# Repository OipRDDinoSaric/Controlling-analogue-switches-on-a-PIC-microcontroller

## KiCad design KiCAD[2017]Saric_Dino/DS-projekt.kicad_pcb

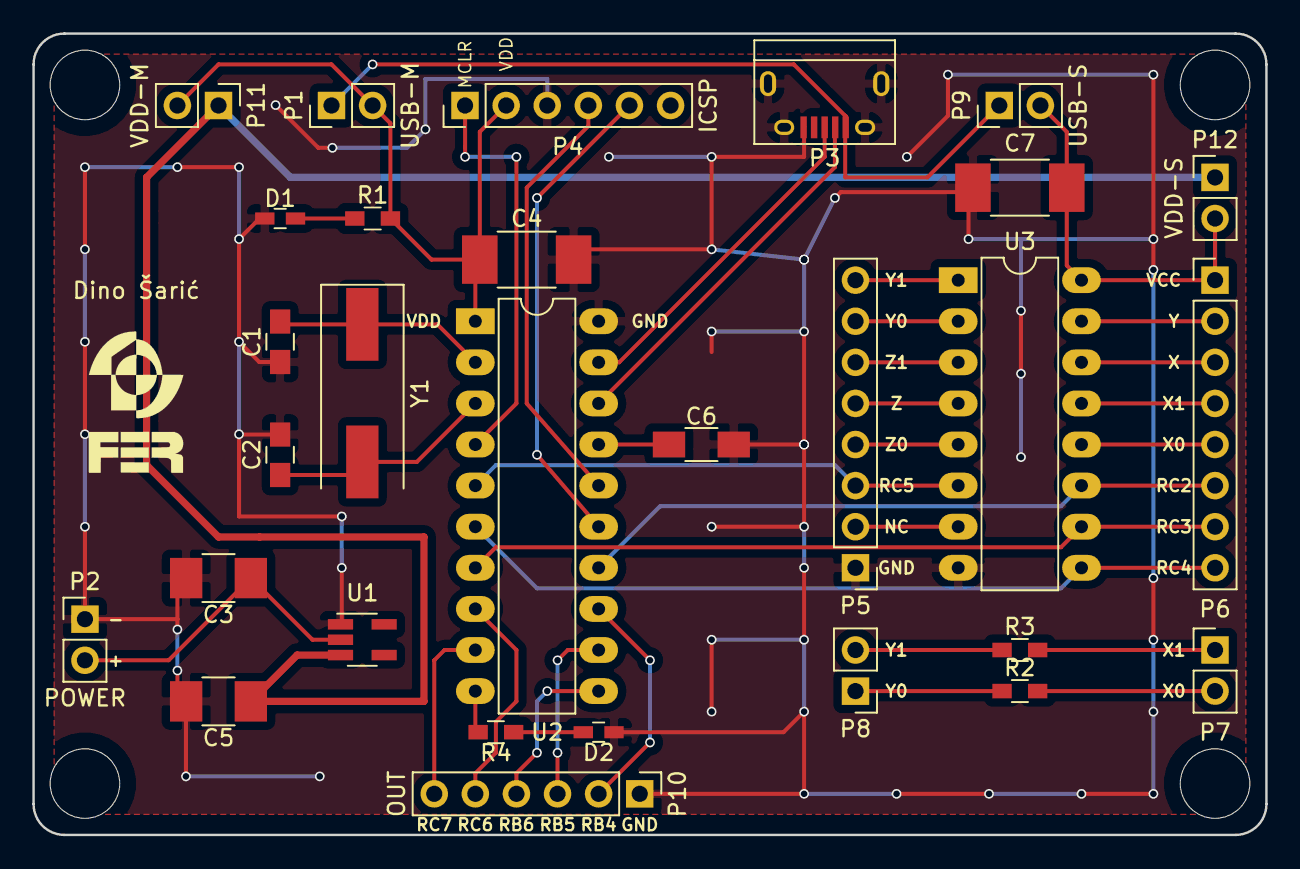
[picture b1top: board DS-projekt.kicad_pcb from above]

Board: 2 copper layers, 76.2 x 49.5 mm, 30 parts (0 on the bottom side), 40 nets.

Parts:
C1, C2: 22 p; C_0805_HandSoldering
C3: 1u; C_1210_HandSoldering
C4: 100 n; C_1812_HandSoldering
C5: 2u2; C_1210_HandSoldering
C6: 470 n; C_1206_HandSoldering
C7: 10 n; C_1812_HandSoldering
D1, D2: LED_Small; C_0603_HandSoldering
P1: USB-M; Pin_Header_Straight_1x02_Pitch2.54mm
P2: POWER; Pin_Header_Straight_1x02_Pitch2.54mm
P3: USB_OTG; USB_Micro-B
P4: ICSP; Pin_Header_Straight_1x06_Pitch2.54mm
P5, P6: CONN_01X08; Pin_Header_Straight_1x08_Pitch2.54mm
P7, P8: CONN_01X02; Pin_Header_Straight_1x02_Pitch2.54mm
P9: USB-S; Pin_Header_Straight_1x02_Pitch2.54mm
P10: OUT; Pin_Header_Straight_1x06_Pitch2.54mm
P11: VDD-M; Pin_Header_Straight_1x02_Pitch2.54mm
P12: VDD-S; Pin_Header_Straight_1x02_Pitch2.54mm
R1, R4: 150; R_0603_HandSoldering
R2: 10k; R_0603_HandSoldering
R3: 100; R_0603_HandSoldering
U1: TPS709B50DBVT; SOT-23-5_HandSoldering
U2: PIC16F1459; DIP-20_W7.62mm_LongPads
U3: MAX4619; DIP-16_W7.62mm_LongPads
VAL: FERlogov3NEGBMP_025in
Y1: Crystal; Crystal_SMD_HC49-SD

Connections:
+5V: C5.1, P11.1, P12.1, U1.3
/CLKIN: C1.2, U2.2, Y1.1
/CLKOUT: C2.1, U2.3, Y1.2
/D+: P3.3, U2.19
/D-: P3.2, U2.18
/ICSPCLK: P4.5, U2.15
/ICSPDAT: P4.4, U2.16
/MCLR: P4.1, U2.4
/RB4: P10.2, U2.13
/RB5: P10.3, U2.12
/RB6: P10.4, U2.11
/RB7: R4.1, U2.10
/RC2: P6.6, U2.14, U3.11
/RC3: P6.7, U2.7, U3.10
/RC4: P6.8, U2.6, U3.9
/RC5: P5.3, U2.5, U3.6
/RC6: P10.5, U2.8
/RC7: P10.6, U2.9
/VBUS_USB: P1.1, P3.1, P9.1
/VDD: C4.2, P1.2, P4.2, P11.2, R1.2, U2.1
/X: P6.3, U3.14
/X0: P6.5, U3.12
/X1: P6.4, U3.13
/Y: P6.2, U3.15
/Y0: P5.7, U3.2
/Y1: P5.8, U3.1
/Z: P5.5, U3.4
/Z0: P5.4, U3.5
/Z1: P5.6, U3.3
GND: C1.1, C2.2, C3.2, C4.1, C5.2, C6.2, C7.1, D1.1, D2.1, P2.1, P3.5, P3.6, P4.3, P5.1, P10.1, U1.1, U2.20, U3.8
unnamed: C3.1, P2.2, U1.2
unnamed: C6.1, U2.17
unnamed: C7.2, P6.1, P9.2, P12.2, U3.16
unnamed: D1.2, R1.1
unnamed: D2.2, R4.2
unnamed: P5.2, U3.7
unnamed: P7.1, R3.2
unnamed: P7.2, R2.2
unnamed: P8.1, R2.1
unnamed: P8.2, R3.1

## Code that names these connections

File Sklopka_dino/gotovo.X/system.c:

/*******************************************************************************
Copyright 2016 Microchip Technology Inc. (www.microchip.com)

Licensed under the Apache License, Version 2.0 (the "License");
you may not use this file except in compliance with the License.
You may obtain a copy of the License at

    http://www.apache.org/licenses/LICENSE-2.0

Unless required by applicable law or agreed to in writing, software
distributed under the License is distributed on an "AS IS" BASIS,
WITHOUT WARRANTIES OR CONDITIONS OF ANY KIND, either express or implied.
See the License for the specific language governing permissions and
limitations under the License.

To request to license the code under the MLA license (www.microchip.com/mla_license), 
please contact mla_licensing@microchip.com
*******************************************************************************/

#include "system.h"
#include "usb.h"

/** CONFIGURATION Bits **********************************************/
// PIC16F1459 configuration bit settings:
#if defined (USE_INTERNAL_OSC)	    // Define this in system.h if using the HFINTOSC for USB operation
    // CONFIG1
    #pragma config FOSC = INTOSC    // Oscillator Selection Bits (INTOSC oscillator: I/O function on CLKIN pin)
    #pragma config WDTE = OFF       // Watchdog Timer Enable (WDT disabled)
    #pragma config PWRTE = OFF      // Power-up Timer Enable (PWRT disabled)
    #pragma config MCLRE = ON       // MCLR Pin Function Select (MCLR/VPP pin function is MCLR)
    #pragma config CP = OFF         // Flash Program Memory Code Protection (Program memory code protection is disabled)
    #pragma config BOREN = OFF      // Brown-out Reset Enable (Brown-out Reset disabled)
    #pragma config CLKOUTEN = ON    // Clock Out Enable (CLKOUT function is enabled on the CLKOUT pin)
    #pragma config IESO = OFF       // Internal/External Switchover Mode (Internal/External Switchover Mode is disabled)
    #pragma config FCMEN = OFF      // Fail-Safe Clock Monitor Enable (Fail-Safe Clock Monitor is disabled)

    // CONFIG2
    #pragma config WRT = OFF        // Flash Memory Self-Write Protection (Write protection off)
    #pragma config CPUDIV = NOCLKDIV// CPU System Clock Selection Bit (NO CPU system divide)
    #pragma config USBLSCLK = 48MHz // USB Low SPeed Clock Selection bit (System clock expects 48 MHz, FS/LS USB CLKENs divide-by is set to 8.)
    #pragma config PLLMULT = 3x     // PLL Multipler Selection Bit (3x Output Frequency Selected)
    #pragma config PLLEN = ENABLED  // PLL Enable Bit (3x or 4x PLL Enabled)
    #pragma config STVREN = ON      // Stack Overflow/Underflow Reset Enable (Stack Overflow or Underflow will cause a Reset)
    #pragma config BORV = LO        // Brown-out Reset Voltage Selection (Brown-out Reset Voltage (Vbor), low trip point selected.)
    #pragma config LPBOR = OFF      // Low-Power Brown Out Reset (Low-Power BOR is disabled)
    #pragma config LVP = ON         // Low-Voltage Programming Enable (Low-voltage programming enabled)
#else
    // CONFIG1
    #pragma config FOSC = HS        // Oscillator Selection Bits (HS Oscillator, High-speed crystal/resonator connected between OSC1 and OSC2 pins)
    #pragma config WDTE = OFF       // Watchdog Timer Enable (WDT disabled)
    #pragma config PWRTE = OFF      // Power-up Timer Enable (PWRT disabled)
    #pragma config MCLRE = OFF      // MCLR Pin Function Select (MCLR/VPP pin function is digital input)
    #pragma config CP = OFF         // Flash Program Memory Code Protection (Program memory code protection is disabled)
    #pragma config BOREN = ON       // Brown-out Reset Enable (Brown-out Reset enabled)
    #pragma config CLKOUTEN = OFF   // Clock Out Enable (CLKOUT function is disabled. I/O or oscillator function on the CLKOUT pin)
    #pragma config IESO = OFF       // Internal/External Switchover Mode (Internal/External Switchover Mode is disabled)
    #pragma config FCMEN = OFF      // Fail-Safe Clock Monitor Enable (Fail-Safe Clock Monitor is disabled)

    // CONFIG2
    #pragma config WRT = OFF        // Flash Memory Self-Write Protection (Write protection off)
    #pragma config CPUDIV = NOCLKDIV// CPU System Clock Selection Bit (NO CPU system divide)
    #pragma config USBLSCLK = 48MHz // USB Low SPeed Clock Selection bit (System clock expects 48 MHz, FS/LS USB CLKENs divide-by is set to 8.)
    #pragma config PLLMULT = 4x     // PLL Multipler Selection Bit (4x Output Frequency Selected)
    #pragma config PLLEN = ENABLED  // PLL Enable Bit (3x or 4x PLL Enabled)
    #pragma config STVREN = ON      // Stack Overflow/Underflow Reset Enable (Stack Overflow or Underflow will cause a Reset)
    #pragma config BORV = LO        // Brown-out Reset Voltage Selection (Brown-out Reset Voltage (Vbor), low trip point selected.)
    #pragma config LPBOR = OFF      // Low-Power Brown Out Reset (Low-Power BOR is disabled)
    #pragma config LVP = OFF        // Low-Voltage Programming Enable (High-voltage on MCLR/VPP must be used for programming)
#endif
/*********************************************************************
* Function: void SYSTEM_Initialize( SYSTEM_STATE state )
*
* Overview: Initializes the system.
*
* PreCondition: None
*
* Input:  SYSTEM_STATE - the state to initialize the system into
*
* Output: None
*
********************************************************************/
void SYSTEM_Initialize( SYSTEM_STATE state )
{
    switch(state)
    {
        case SYSTEM_STATE_USB_START:
            #if defined(USE_INTERNAL_OSC)
                //Make sure to turn on active clock tuning for USB full speed 
                //operation from the INTOSC
                OSCCON = 0xFC;  //HFINTOSC @ 16MHz, 3X PLL, PLL enabled
                ACTCON = 0x90;  //Active clock tuning enabled for USB
            #endif
            //LED_Enable(LED_USB_DEVICE_STATE);
            //BUTTON_Enable(BUTTON_DEVICE_CDC_BASIC_DEMO);
            break;
            
        case SYSTEM_STATE_USB_SUSPEND: 
            break;
            
        case SYSTEM_STATE_USB_RESUME:
            break;
    }
}

			
			
void interrupt SYS_InterruptHigh(void)
{
    #if defined(USB_INTERRUPT)
        USBDeviceTasks();
    #endif
}
